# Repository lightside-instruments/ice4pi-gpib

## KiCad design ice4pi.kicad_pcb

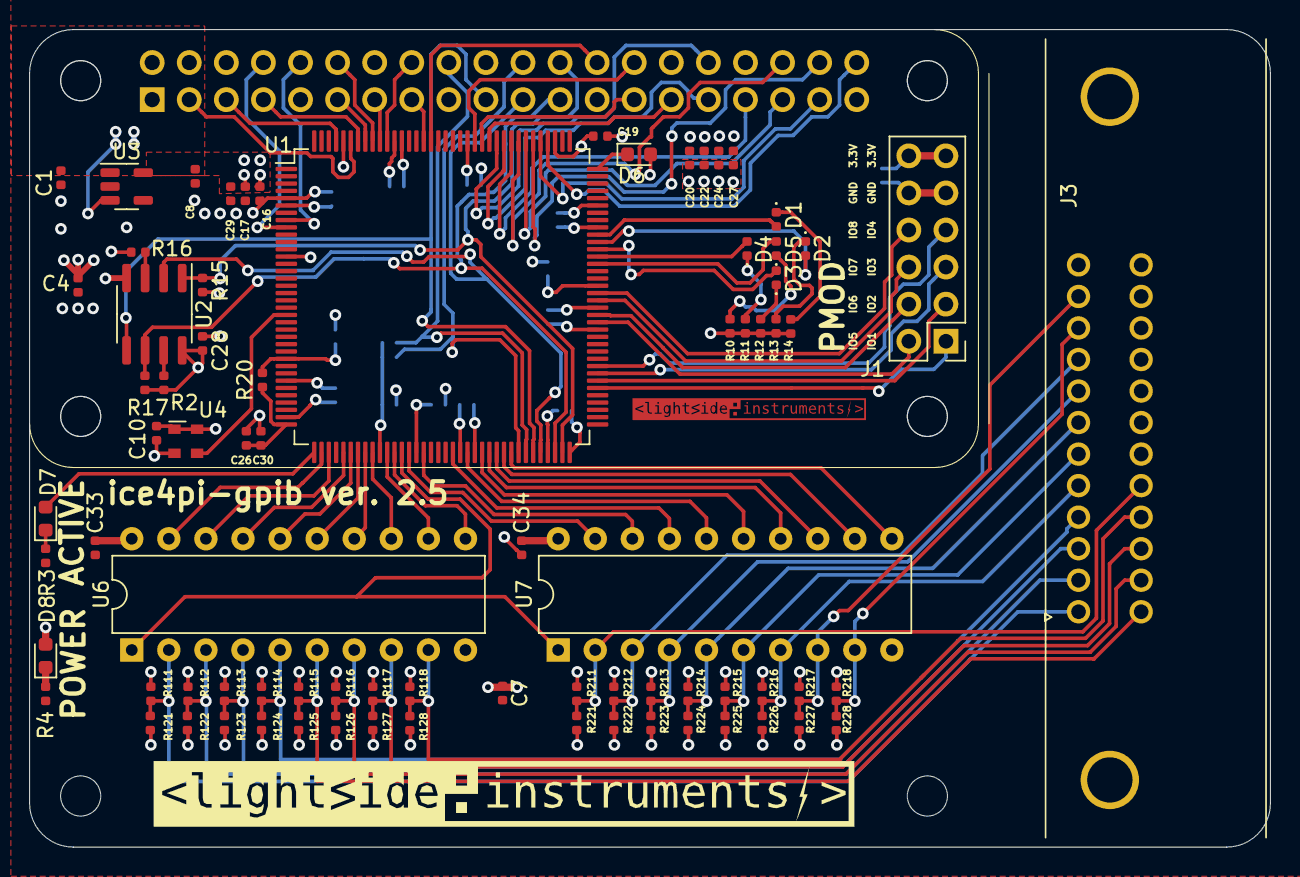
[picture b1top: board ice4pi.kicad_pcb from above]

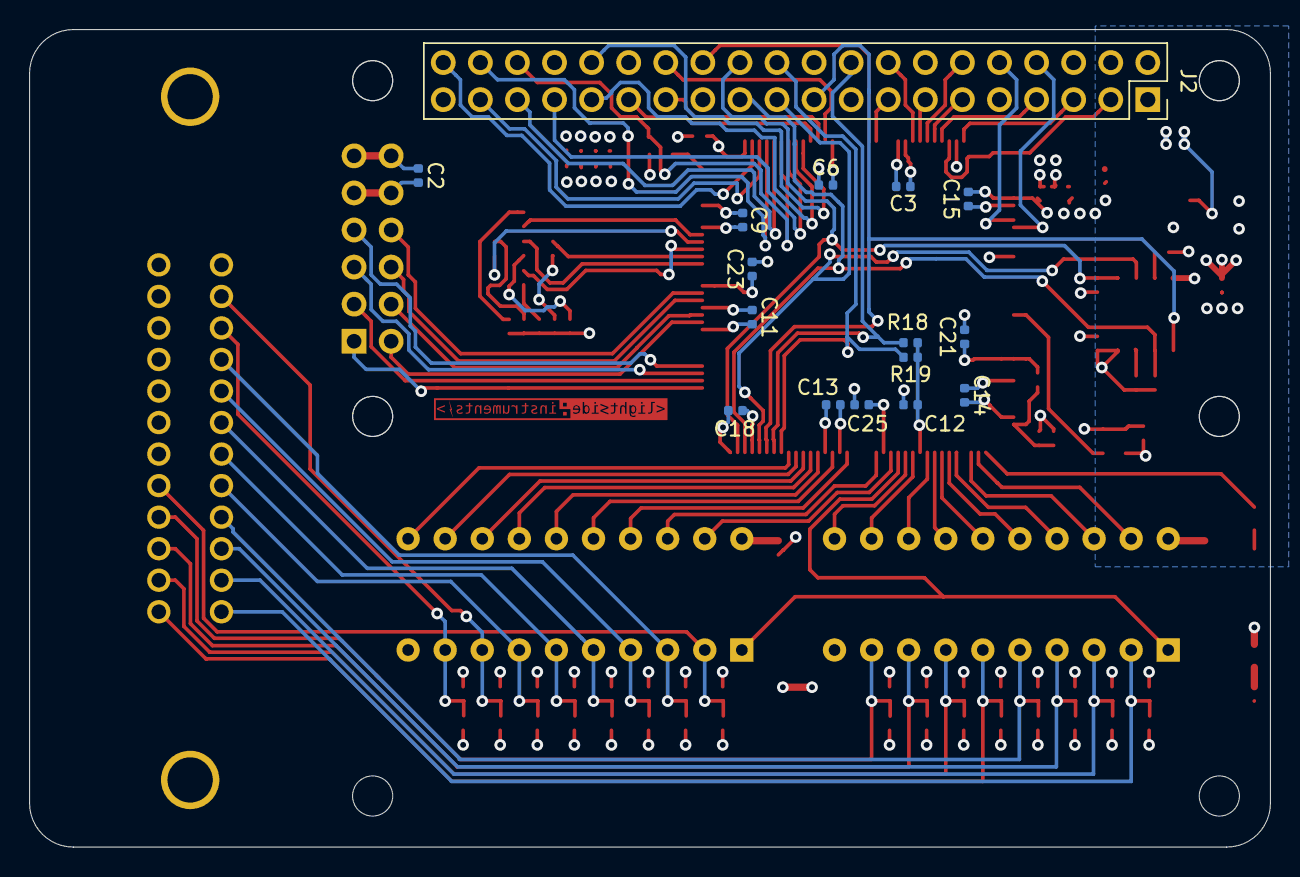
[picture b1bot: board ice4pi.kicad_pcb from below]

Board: 4 copper layers, 85.0 x 56.0 mm, 96 parts (16 on the bottom side), 93 nets.

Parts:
C1, C4, C16, C20, C30: 10uF; C_0402_1005Metric
C2, C3, C9, C12, C14, C18, C19, C21, C23, C24, C25, C26, C28: 0.1uF; C_0402_1005Metric
C6, C10, C11, C13, C15, C27, C29: 0.01uF; C_0402_1005Metric
C7: 10 uF; C_0402_1005Metric
C8: 4.7uF; C_0402_1005Metric
C17, C22: 1 uF; C_0402_1005Metric
C33, C34: 220 nF; C_0402_1005Metric
D1, D2, D3, D4, D5: LED; LED_0402_1005Metric
D6: CDBU0520; D_0603_1608Metric
D7, D8: LED; LED_0603_1608Metric
J1: Pmod 2x6; PinSocket_2x06_P2.54mm_Vertical_1to6_7to12
J2: raspberry_pi_2_3_4_ordered; PinSocket_2x20_P2.54mm_Vertical_1_04mm
J3: Conn_02x12_Top_Bottom; centronix-24-male
R2, R15, R16, R17, R18, R19: 10K; R_0402_1005Metric
R3, R4, R10, R11, R12, R13, R14: 1K; R_0402_1005Metric
R20: 100; R_0402_1005Metric
R111, R112, R113, R114, R115, R116, R117, R118, R211, R212, R213, R214, R215, R216, R217, R218: 3.3K; R_0402_1005Metric
R121, R122, R123, R124, R125, R126, R127, R128, R221, R222, R223, R224, R225, R226, R227, R228: 6.2K; R_0402_1005Metric
U1: ICE40HX1K-TQ144; TQFP-144_20x20mm_P0.5mm
U2: W25Q32JVSSIQ; SOIC-8_3.9x4.9mm_P1.27mm
U3: MIC5504-1.2YM5; SOT-23-5
U4: DSC1001DI1-012.0000; Oscillator_SMD_Abracon_ASDMB-4Pin_2.5x2.0mm
U6: SN75160BN; DIP-20_W7.62mm
U7: SN75161BN; DIP-20_W7.62mm
svg2mod: G***; lsi-logo-16mm-fcu
svg2mod#2: G***; lsi-logo-48mm

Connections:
12MHz: U1.21 (IOL_7A_GBIN6), U4.3 (Out)
+1V2: C8.1, C16.1, C17.1, C19.1, C21.1, C23.1, C25.1, C29.1, R20.1, U1.27 (VCC), U1.51 (VCC), U1.92 (VCC), U1.111 (VCC), U3.5 (VOUT)
+3V3: C2.1, C3.1, C4.1, C6.1, C9.1, C10.1, C11.1, C12.1, C13.1, C14.1, C15.1, C18.1, C20.1, C22.1, C24.1, C27.1, C28.1, D6.2 (A), J1.6, J1.12, J2.1 (3V3), J2.17 (3V3), R2.1, R15.1, R16.1, R17.1, R18.1, R19.1, U1.6 (VCCIO_3), U1.30 (VCCIO_3), U1.46 (VCCIO_2), U1.57 (VCCIO_2), U1.72 (VCC_SPI), U1.89 (VCCIO_1), U1.100 (VCCIO_1), U1.123 (VCCIO_0), U1.133 (VCCIO_0), U2.8 (VCC), U4.1 (Standby), U4.4 (VDD)
+5V: C1.1, C7.1, C33.1, C34.1, D8.2 (A), J2.2 (5V), J2.4 (5V), R111.1, R112.1, R113.1, R114.1, R115.1, R116.1, R117.1, R118.1, R211.1, R212.1, R213.1, R214.1, R215.1, R216.1, R217.1, R218.1, U3.1 (VIN), U3.3 (EN), U6.20 (VCC), U7.20 (VCC)
/gpib4ice/ATN: J3.11, R217.2, R227.1, U7.8 (ATN)
/gpib4ice/DAV: J3.6, R215.2, R225.1, U7.6 (DAV)
/gpib4ice/DIO01: J3.1, R111.2, R121.1, U6.2 (B1)
/gpib4ice/DIO02: J3.2, R112.2, R122.1, U6.3 (B2)
/gpib4ice/DIO03: J3.3, R113.2, R123.1, U6.4 (B3)
/gpib4ice/DIO04: J3.4, R114.2, R124.1, U6.5 (B4)
/gpib4ice/DIO05: J3.13, R115.2, R125.1, U6.6 (B5)
/gpib4ice/DIO06: J3.14, R116.2, R126.1, U6.7 (B6)
/gpib4ice/DIO07: J3.15, R117.2, R127.1, U6.8 (B7)
/gpib4ice/DIO08: J3.16, R118.2, R128.1, U6.9 (B8)
/gpib4ice/EOI: J3.5, R216.2, R226.1, U7.7 (EOI)
/gpib4ice/IFC: J3.9, R212.2, R222.1, U7.3 (IFC)
/gpib4ice/NDAC: J3.8, R213.2, R223.1, U7.4 (NDAC)
/gpib4ice/NRFD: J3.7, R214.2, R224.1, U7.5 (NRFD)
/gpib4ice/REN: J3.17, R211.2, R221.1, U7.2 (REN)
/gpib4ice/SRQ: J3.10, R218.2, R228.1, U7.9 (SRQ)
CTRL_LED: D7.2 (A), U1.37 (IOB_24)
GND: C1.2, C2.2, C3.2, C4.2, C6.2, C7.2, C8.2, C9.2, C10.2, C11.2, C12.2, C13.2, C14.2, C15.2, C16.2, C17.2, C18.2, C19.2, C20.2, C21.2, C22.2, C23.2, C24.2, C25.2, C26.2, C27.2, C28.2, C29.2, C30.2, C33.2, C34.2, J1.5, J1.11, J2.6 (GND), J2.9 (GND), J2.14 (GND), J2.20 (GND), J2.25 (GND), J2.30 (GND), J2.34 (GND), J2.39 (GND), J3.12, J3.18, J3.19, J3.20, J3.21, J3.22, J3.23, J3.24, R3.2, R4.2, R10.2, R11.2, R12.2, R13.2, R14.2, R121.2, R122.2, R123.2, R124.2, R125.2, R126.2, R127.2, R128.2, R221.2, R222.2, R223.2, R224.2, R225.2, R226.2, R227.2, R228.2, U1.5 (GND), U1.13 (GND), U1.14 (GND), U1.35 (GNDPLL), U1.59 (GND), U1.69 (GND), U1.86 (GND), U1.103 (GND), U1.132 (GND), U1.140 (GND), U2.4 (GND), U3.2 (GND), U4.2 (GND), U6.10 (GND), U7.10 (GND)
GPIB_ATN: U1.62 (IOB_41), U7.13 (ATN)
GPIB_DAV: U1.60 (IOB_39), U7.15 (DAV)
GPIB_DC: U1.64 (IOB_43_CBSEL1), U7.11 (DC)
GPIB_DIO01: U1.38 (IOB_25), U6.19 (D1)
GPIB_DIO02: U1.39 (IOB_26), U6.18 (D2)
GPIB_DIO03: U1.41 (IOB_27), U6.17 (D3)
GPIB_DIO04: U1.42 (IOB_28), U6.16 (D4)
GPIB_DIO05: U1.43 (IOB_29), U6.15 (D5)
GPIB_DIO06: U1.44 (IOB_30), U6.14 (D6)
GPIB_DIO07: U1.45 (IOB_31), U6.13 (D7)
GPIB_DIO08: U1.47 (IOB_32), U6.12 (D8)
GPIB_EOI: U1.61 (IOB_40), U7.14 (EOI)
GPIB_IFC: U1.52 (IOB_34), U7.18 (IFC)
GPIB_NDAC: U1.56 (IOB_37), U7.17 (NDAC)
GPIB_NRFD: U1.58 (IOB_38), U7.16 (NRFD)
GPIB_PE: U1.48 (IOB_33), U6.11 (~PE)
GPIB_REN: U1.50 (IOB_36_GBIN4), U7.19 (REN)
GPIB_SRQ: U1.63 (IOB_42_CBSEL0), U7.12 (SRQ)
GPIB_TE: U1.49 (IOB_35_GBIN5), U6.1 (TE), U7.1 (TE)
LED0: D1.2 (A), U1.99 (IOR_66)
LED1: D2.2 (A), U1.98 (IOR_65)
LED2: D3.2 (A), U1.97 (IOR_64)
LED3: D4.2 (A), U1.96 (IOR_63)
LED4: D5.2 (A), U1.95 (IOR_62)
unnamed: C26.1, C30.1, R20.2, U1.36 (VCCPLL)
unnamed: D1.1 (K), R14.1
unnamed: D2.1 (K), R13.1
unnamed: D3.1 (K), R12.1
unnamed: D4.1 (K), R11.1
unnamed: D5.1 (K), R10.1
unnamed: D6.1 (K), U1.108 (VPP_2V5)
unnamed: D7.1 (K), R3.1
unnamed: D8.1 (K), R4.1
unnamed: R2.2, U2.7 (~HOLD)
unnamed: R16.2, U2.3 (~WP)
PIO0_02: J2.40 (GPIO21/SCLK1), U1.112 (IOT_73)
PIO0_03: J2.37 (GPIO26), U1.113 (IOT_74)
PIO0_04: J2.38 (GPIO20/MOSI1), U1.114 (IOT_75)
PIO0_05: J2.35 (GPIO19/MISO1), U1.115 (IOT_76)
PIO0_06: J2.36 (GPIO16), U1.116 (IOT_77)
PIO0_07: J2.33 (PWM1/GPIO13), U1.117 (IOT_78)
PIO0_08: J2.31 (GCLK2/GPIO6), U1.118 (IOT_79)
PIO0_09: J2.32 (PWM0/GPIO12), U1.119 (IOT_80)
PIO0_10: J2.29 (GCLK1/GPIO5), U1.120 (IOT_81)
PIO0_11: J2.27 (ID_SD/GPIO0), U1.121 (IOT_82)
PIO0_12: J2.28 (ID_SC/GPIO1), U1.122 (IOT_83)
PIO0_13: J2.26 (~CE1/GPIO7), U1.128 (IOT_84_GBIN1)
PIO0_14: J2.15 (GPIO22), U1.129 (IOT_85_GBIN0)
PIO0_15: J2.16 (GPIO23), U1.134 (IOT_87)
PIO0_16: J2.13 (GPIO27), U1.135 (IOT_88)
PIO0_17: J2.12 (GPIO18/PWM0), U1.136 (IOT_89)
PIO0_18: J2.11 (GPIO17), U1.137 (IOT_90)
PIO0_19: J2.7 (GCLK0/GPIO4), U1.138 (IOT_91)
PIO0_20: J2.3 (SDA/GPIO2), U1.139 (IOT_92)
PIO0_21: J2.5 (SCL/GPIO3), U1.141 (IOT_93)
PIO1_02: J1.1, U1.78 (IOR_52)
PIO1_03: J1.2, U1.79 (IOR_53)
PIO1_04: J1.3, U1.80 (IOR_54)
PIO1_05: J1.4, U1.81 (IOR_55)
PIO1_06: J1.7, U1.87 (IOR_56)
PIO1_07: J1.8, U1.88 (IOR_57)
PIO1_08: J1.9, U1.90 (IOR_58)
PIO1_09: J1.10, U1.91 (IOR_59)
RS232_Rx_TTL: J2.8 (GPIO14/TXD), U1.9 (IOL_4A)
RS232_Tx_TTL: J2.10 (GPIO15/RXD), U1.8 (IOL_3B)
iCE_CDONE: J2.22 (GPIO25), R19.2, U1.65 (CDONE)
iCE_CREST: J2.18 (GPIO24), R18.2, U1.66 (~CRESET_B)
iCE_MISO: J2.21 (MISO0/GPIO9), U1.68 (IOB_45_SDI), U2.2 (SDO)
iCE_MOSI: J2.19 (MOSI0/GPIO10), U1.67 (IOB_44_SDO), U2.5 (SDI)
iCE_SCK: J2.23 (SCLK0/GPIO11), R17.2, U1.70 (IOB_46_SCK), U2.6 (SCK)
iCE_SS_B: J2.24 (~CE0/GPIO8), R15.2, U1.71 (IOB_47_SS), U2.1 (~CS)

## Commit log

2024-09-30 ice4pi-gpib-2.5
